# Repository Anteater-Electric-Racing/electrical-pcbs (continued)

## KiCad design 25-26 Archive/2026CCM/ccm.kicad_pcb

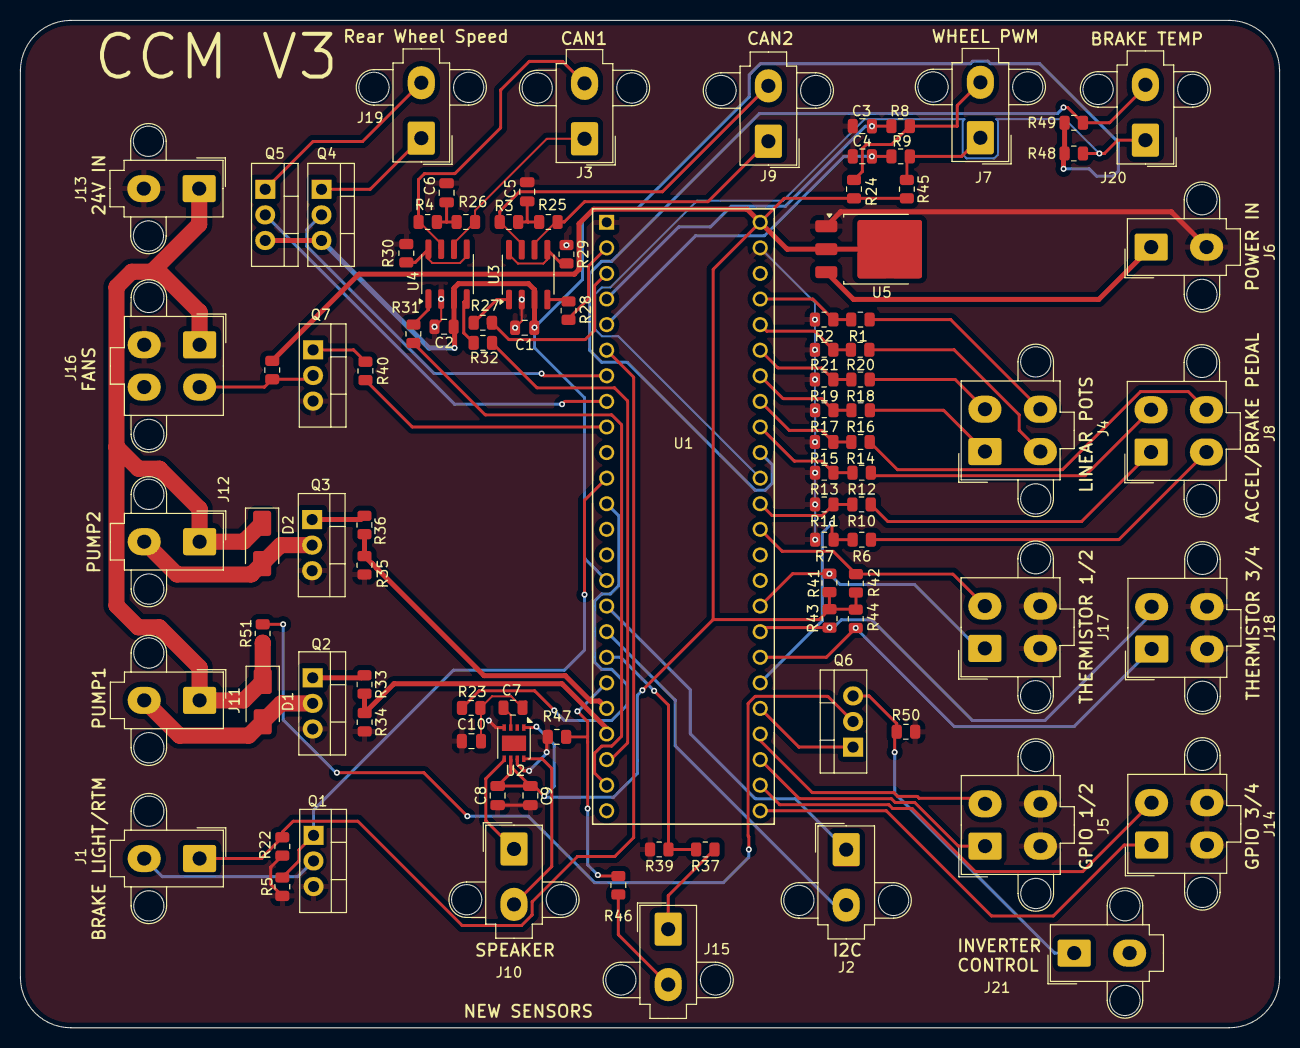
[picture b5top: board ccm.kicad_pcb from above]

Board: 2 copper layers, 125.0 x 100.0 mm, 96 parts (0 on the bottom side), 81 nets.

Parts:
C1, C2, C5, C6: 100 nF; C_0805_2012Metric
C3, C4: 0.01uF; C_0805_2012Metric
C7: 0.1uF; C_0805_2012Metric
C8: 1uF; C_0805_2012Metric
C9: 10uF; C_0805_2012Metric
C10: 10nF; C_0805_2012Metric
D1, D2: SS34; D_SMA
J1, J2, J3, J6, J7, J9, J10, J11, J12, J13, J15, J19, J20, J21: Conn_01x02_Socket; Molex_Mini-Fit_Jr_5566-02A2_2x01_P4.20mm_Vertical
J4, J5, J8, J14, J16, J17, J18: Conn_01x04_Socket; Molex_Mini-Fit_Jr_5566-04A2_2x02_P4.20mm_Vertical
Q1, Q2, Q3, Q4, Q5, Q6, Q7: IRLZ34N; TO-220-3_Vertical
R1, R6, R10, R12, R14, R16, R18, R20: 50k; R_0805_2012Metric
R2, R7, R11, R13, R15, R17, R19, R21: 97k; R_0805_2012Metric
R3, R4, R25, R26, R27, R28, R29, R30, R31, R32: 60; R_0805_2012Metric
R5, R22, R34, R35, R38, R41, R42, R43, R44, R47, R50, R51: 10k; R_0805_2012Metric
R8, R9: 10; R_0805_2012Metric
R23, R40: 1k; R_0805_2012Metric
R24, R45, R48, R49: 4.7k; R_0805_2012Metric
R33, R36: 220; R_0805_2012Metric
R37: 100k; R_0805_2012Metric
R39: 27k; R_0805_2012Metric
R46: 6.5k; R_0805_2012Metric
U1: Teensy4.1; CONN_4848-6000-CP_3MM
U2: PAM8302AAY; DFN-8-1EP_3x3mm_P0.65mm_EP1.55x2.4mm
U3, U4: SN65HVD230; SOIC-8_3.9x4.9mm_P1.27mm
U5: LM1117DT-5.0; TO-252-3_TabPin2

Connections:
+3.3V: C1.1, C2.1, Q4.3 (S), Q5.3 (S), R48.1, R49.1, U1.15 (3V3), U3.3 (VCC), U4.3 (VCC)
+5V: C8.1, C9.1, R24.2, R38.1, R41.2, R42.2, R43.2, R44.2, R45.2, U1.48 (VIN), U2.1 (~SD), U2.6 (VDD), U5.2 (VO)
CANH_1: J9.2, R3.1, U3.7 (CANH)
CANH_2: J3.2, R4.1, U4.7 (CANH)
CANL_1: J9.1, R25.2, U3.6 (CANL)
CANL_2: J3.1, R26.2, U4.6 (CANL)
CAN_RX_1: R28.1, U1.2 (0_RX1_CRX2_CS1)
CAN_RX_2: R32.1, U1.22 (30_CRX3)
CAN_TX_1: R27.1, U1.3 (1_TX1_CTX2_MISO1)
CAN_TX_2: R31.1, U1.23 (31_CTX3)
Fan+: D1.1 (K), D2.1 (K), J11.1, J12.1, J13.1, J16.1, R51.1
Fan_PWM: J16.2, Q7.2 (D), R38.2
GLV-: C1.2, C2.2, C3.2, C4.2, C5.2, C6.2, C8.2, C9.2, C10.1, J5.3, J5.4, J6.2, J13.2, J14.3, J14.4, J16.3, J17.3, J17.4, J18.3, J18.4, Q1.3 (S), Q2.3 (S), Q3.3 (S), Q7.3 (S), R2.2, R5.1, R7.2, R11.2, R13.2, R15.2, R17.2, R19.2, R21.2, R22.1, R29.1, R30.1, R34.2, R35.2, R39.2, R47.2, R50.2, U1.1 (GND), U1.47 (GND), U2.4 (IN-), U2.7 (GND), U3.2 (GND), U4.2 (GND), U5.1 (GND)
unnamed: C5.1, R3.2, R25.1
unnamed: C6.1, R4.2, R26.1
unnamed: C7.2, C10.2, R23.1
unnamed: Q1.1 (G), R5.2, U1.11 (9_OUT1C)
unnamed: Q2.1 (G), R33.1
unnamed: Q3.1 (G), R36.1
unnamed: Q4.2 (D), U1.7 (5_IN2)
unnamed: Q5.2 (D), U1.8 (6_OUT1D)
unnamed: Q6.2 (D), R51.2
unnamed: Q6.1 (G), U1.29 (37_CS)
unnamed: Q7.1 (G), R40.1
unnamed: C3.1, R8.2, U1.4 (2_OUT2)
unnamed: C4.1, R9.2, U1.5 (3_LRCLK2)
unnamed: R40.2, U1.9 (7_RX2_OUT1A)
unnamed: R10.2, R11.1, U1.37 (15_A1_RX3_SPDIF_IN)
unnamed: R12.2, R13.1, U1.40 (18_A4_SDA)
unnamed: R14.2, R15.1, U1.41 (19_A5_SCL)
unnamed: R16.2, R17.1, U1.42 (20_A6_TX5_LRCLK1)
unnamed: R18.2, R19.1, U1.43 (21_A7_RX5_BCLK1)
unnamed: R20.2, R21.1, U1.44 (22_A8_CTX1)
unnamed: R1.2, R2.1, U1.45 (23_A9_CRX1_MCLK1)
unnamed: R37.2, R39.1, U1.18 (26_A12_MOSI1)
unnamed: R46.2, R47.1, U1.19 (27_A13_SCK1)
unnamed: R35.1, R36.2, U1.20 (28_RX7)
unnamed: R33.2, R34.1, U1.21 (29_TX7)
unnamed: R6.2, R7.1, U1.30 (38_CS1_IN1)
unnamed: C7.1, U2.3 (IN+)
unnamed: R27.2, U3.1 (D)
unnamed: R28.2, U3.4 (R)
unnamed: R29.2, U3.5 (Vref), U3.8 (Rs)
unnamed: R31.2, U4.1 (D)
unnamed: R32.2, U4.4 (R)
unnamed: R30.2, U4.5 (Vref), U4.8 (Rs)
PWM_in_1: J7.1, R9.1, R45.1
PWM_in_2: J7.2, R8.1, R24.1
Pump1-: D1.2 (A), J11.2, Q2.2 (D)
Pump2-: D2.2 (A), J12.2, Q3.2 (D)
Vin: J6.1, U5.3 (VI)
acc_ped_1: J8.4, R14.1
acc_ped_2: J8.2, R12.1
brake_1: J8.1, R10.1
brake_2: J8.3, R6.1
brake_light: J1.2, Q1.2 (D)
brake_temp_scl: J20.1, R48.2, U1.38 (16_A2_RX4_SCL1)
brake_temp_sda: J20.2, R49.2, U1.39 (17_A3_TX4_SDA1)
gpio1: J5.2, U1.28 (36_CS)
gpio2: J5.1, U1.27 (35_TX8)
gpio3: J14.2, U1.26 (34_RX8)
gpio4: J14.1, U1.25 (33_MCLK2)
i2c_SCL: J2.1, U1.16 (24_A10_TX6_SCL2)
i2c_SDA: J2.2, U1.17 (25_A11_RX6_SDA2)
kl15: J21.1, Q6.3 (S), R50.1
lin_pot_1: J4.4, R1.1
lin_pot_2: J4.3, R20.1
lin_pot_3: J4.2, R18.1
lin_pot_4: J4.1, R16.1
ready_to_drive_button: J1.1, R22.2, U1.6 (4_BCLK2)
shock_travel: J15.2, R46.1
speaker+: J10.1, U2.5 (OUT+)
speaker-: J10.2, U2.8 (OUT-)
speaker_pwm: R23.2, U1.12 (10_CS_MQSR)
steering_angle: J15.1, R37.1
thermistor1+: J17.2, R41.1, U1.36 (14_A0_TX3_SPDIF_OUT)
thermistor2+: J17.1, R42.1, U1.33 (41_A17)
thermistor3+: J18.2, R43.1, U1.32 (40_A16)
thermistor4+: J18.1, R44.1, U1.31 (39_MISO1_OUT1A)
wheelspeed1: J19.1, Q4.1 (G)
wheelspeed2: J19.2, Q5.1 (G)

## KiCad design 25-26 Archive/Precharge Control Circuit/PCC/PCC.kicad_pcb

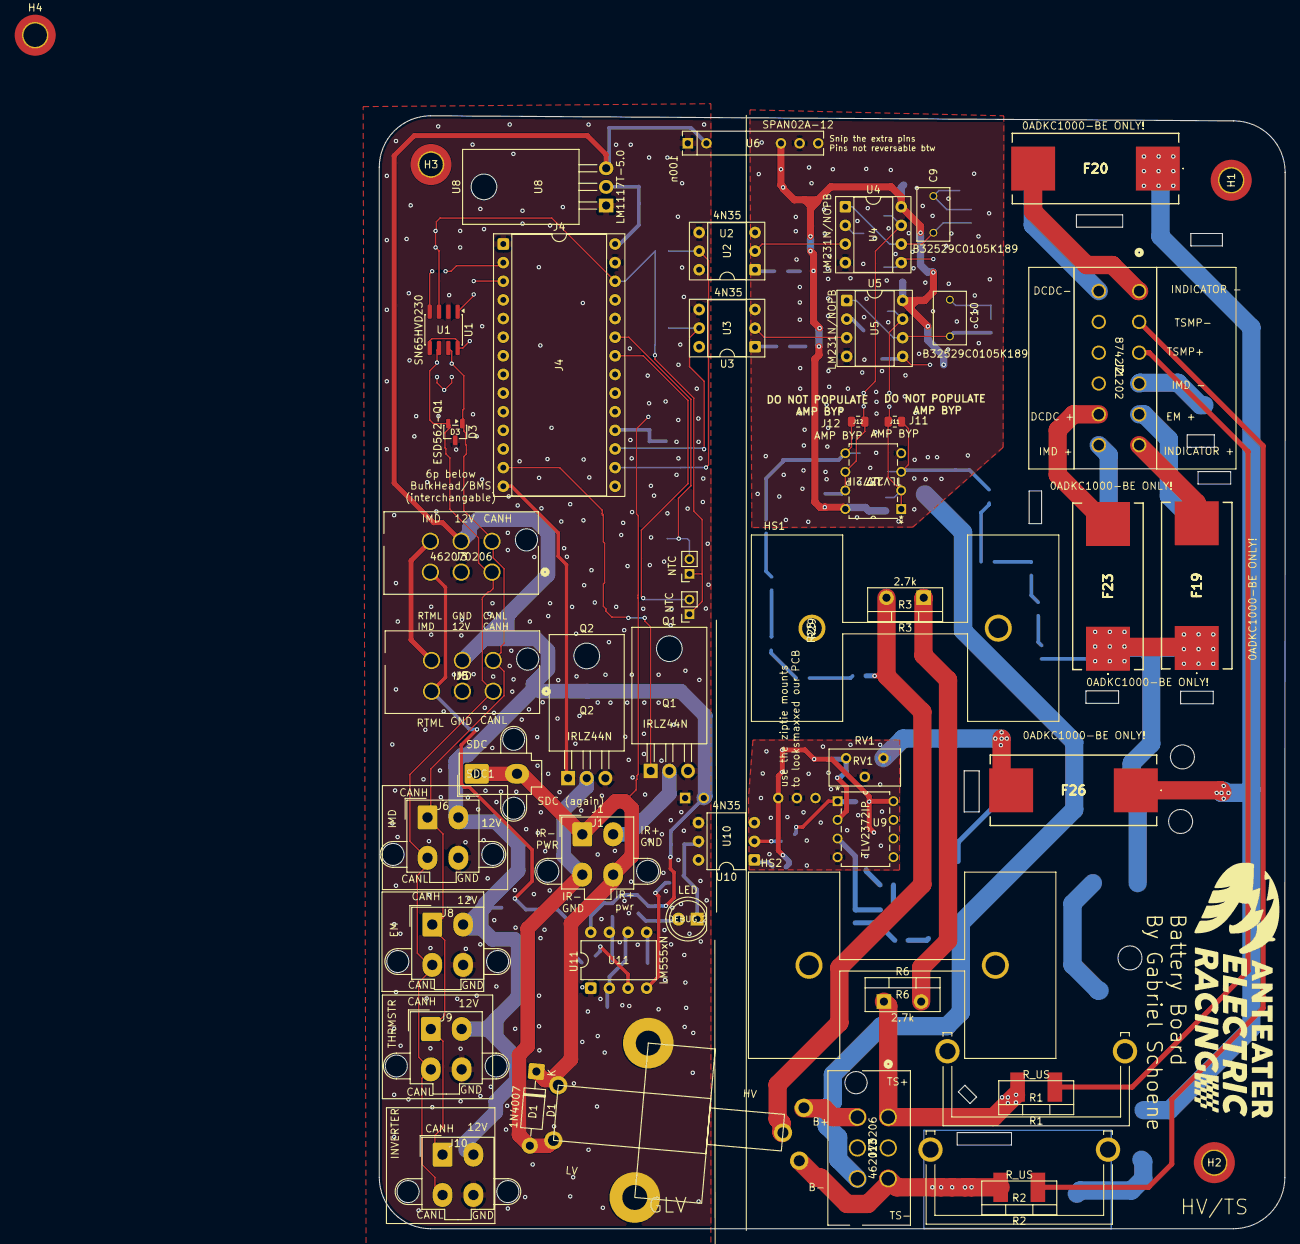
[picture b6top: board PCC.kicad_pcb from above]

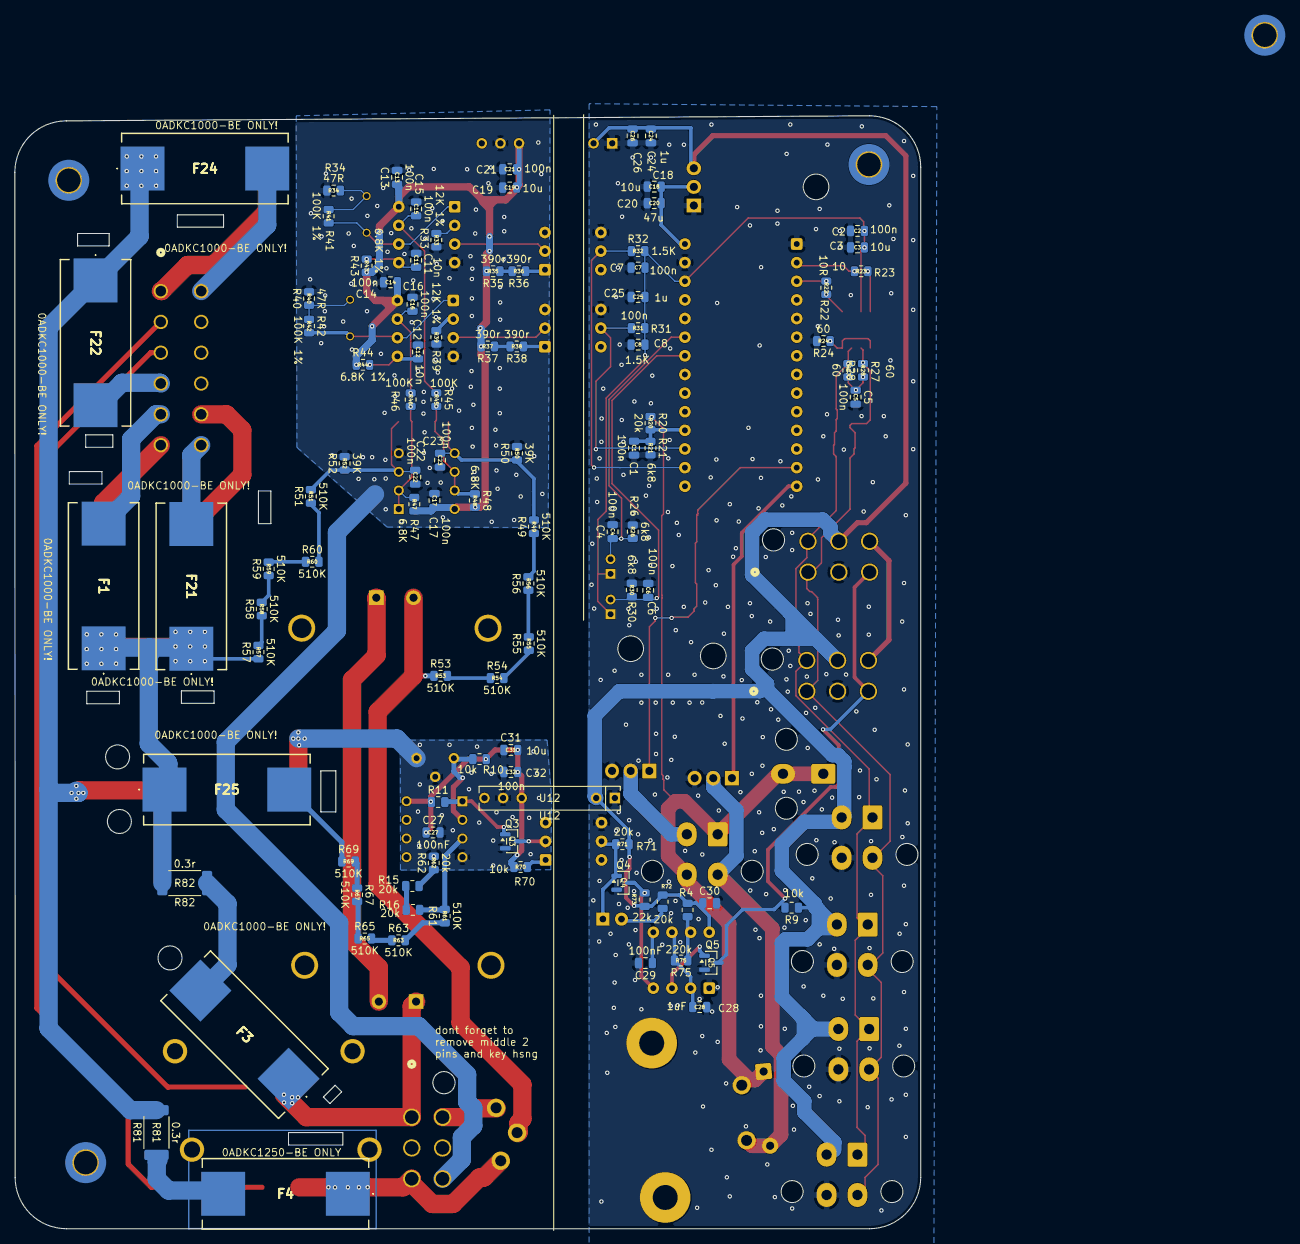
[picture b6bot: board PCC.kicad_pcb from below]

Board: 2 copper layers, 123.5 x 151.7 mm, 150 parts (99 on the bottom side), 93 nets.

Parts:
C1, C2, C4, C5, C6, C7, C8, C13, C14, C15, C16, C17, C21, C22, C23, C26, C32: 100n; C_0805_2012Metric
C3, C18, C19, C31: 10u; C_0805_2012Metric
C9, C10: B32529C0105K189; CAPRR500W50L730T450H950
C11, C12: 10n; C_0805_2012Metric
C20: 47u; C_0805_2012Metric
C24, C25: 1u; C_0805_2012Metric
C27, C29, C30: 100nF; C_0805_2012Metric
C28: 1uF; C_0805_2012Metric
D1: 1N4007; D_DO-41_SOD81_P10.16mm_Horizontal
D3: ESD562-Q1; SOT-23-3
DEBUG_2: LED; LED_D5.0mm
F1, F19, F20, F21, F22, F23, F24, F25, F26: 1A; 5x20fuseblock
F3, F4: 1.25; 5x20fuseblock
H1, H2, H3, H4: MountingHole_Pad; MountingHole_3.2mm_M3_DIN965_Pad_TopBottom
HS1, HS2: Heatsink_Pad; heatsink
HS3, HS4: Heatsink_Pad; smolsink
J1: Conn_01x04_Socket; Molex_Mini-Fit_Jr_5566-04A2_2x02_P4.20mm_Vertical
J2: 874271202; 12pSTminifit
J3, J13: 462070206; 6pMinifitJR
J4: Conn_02x14_Counter_Clockwise; DIP-28_W15.24mm_Socket
J5: IMD; 6pMinifitJR
J6: Thermistor Expansion; Molex_Mini-Fit_Jr_5566-04A2_2x02_P4.20mm_Vertical
J8: BMS; Molex_Mini-Fit_Jr_5566-04A2_2x02_P4.20mm_Vertical
J9: EnergyMeter; Molex_Mini-Fit_Jr_5566-04A2_2x02_P4.20mm_Vertical
J10: INVTR; Molex_Mini-Fit_Jr_5566-04A2_2x02_P4.20mm_Vertical
J11, J12: AMP BYP; R_0805_2012Metric
K1: Relay_SPDT; RH3_Mount
Q1, Q2: IRLZ44N; TO-220-3_Horizontal_TabDown
Q3, Q4, Q5: Q_NMOS_GSD; SOT-23
R1, R2: R_US; TO-220-2_Vertical-SMD
R3, R6: 2.7k; TO-220-2_Vertical
R4, R73: 22k; R_0805_2012Metric
R9, R10, R11, R70: 10k; R_0805_2012Metric
R15, R16, R20, R62, R71, R72: 20k; R_0805_2012Metric
R21, R26, R30: 6k8; R_0805_2012Metric
R22: 10R; R_0805_2012Metric
R23: 10; R_0805_2012Metric
R24, R27, R28: 60; R_0805_2012Metric
R25, R29: NTC; PinSocket_1x02_P2.00mm_Vertical
R31, R32: 1.5K; R_0805_2012Metric
R33, R39: 12K 1%; R_0805_2012Metric
R34, R40: 47R; R_0805_2012Metric
R35, R36, R37, R38: 390r; R_0805_2012Metric
R41, R42: 100K 1%; R_0805_2012Metric
R43, R44: 6.8K 1%; R_0805_2012Metric
R45, R46: 100K; R_0805_2012Metric
R47, R48: 6.8K; R_0805_2012Metric
R49, R51, R53, R54, R55, R56, R57, R58, R59, R60, R61, R63, R65, R67, R69: 510K; R_0805_2012Metric
R50, R52: 39K; R_0805_2012Metric
R75: 220k; R_0805_2012Metric
R81, R82: 0.3r; R_2512_6332Metric_Pad1.40x3.35mm_HandSolder
RV1: 1k default (1-5k); Potentiometer_Bourns_3296Y_Vertical
SDC1: Conn_01x02_Socket; Molex_Mini-Fit_Jr_5566-02A2_2x01_P4.20mm_Vertical
U1: SN65HVD230; SOIC-8_3.9x4.9mm_P1.27mm
U2, U3: 4N35; DIP-6_W7.62mm_Socket
U4, U5: DIP-8_W7.62mm_Socket
U6, U12: isoDCDC(removedPins)
U7, U9: TLV2372IP; P8
U8: LM1117T-5.0; TO-220-3_Horizontal_TabDown
U10: 4N35; DIP-6_W7.62mm
U11: LM555xN; DIP-8_W7.62mm

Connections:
12V_UNISO: C27.1, C31.2, C32.2, R10.1, R11.1, R70.1, U9.8 (VDD), U12.6 (+Vout)
+3.3V: C2.1, C3.1, C7.1, C8.1, C25.1, J4.26, R25.1, R29.1, R31.2, R32.2, U1.3 (VCC)
+5V: C18.1, C20.1, J4.28, U8.2 (VO)
+12 ISO: C13.1, C14.1, C17.1, C19.2, C21.2, R35.2, R37.2, R43.1, R44.1, R47.2, R48.2, U4.8 (VS), U5.8 (VS), U6.6 (+Vout), U7.8 (VDD)
/FusedTS + (IMD): F21.2, J2.12
/FusedTS + (expansion): F23.2, J2.11
/FusedTS + (indicator): F19.2, J2.6
/FusedTS - (IMD): F22.2, J2.4
/FusedTS - (expansion): F24.2, J2.7
/FusedTS - (indicator): F20.2, J2.1
/FusedTS+ (EM): F1.2, J2.5
/NTC 1: C4.1, J4.23, R25.2, R26.1
/NTC 2: C6.1, J4.22, R29.2, R30.1
/SDN signal: C1.1, J4.18, R20.2, R21.1
/TSMP+: J2.3, R1.1
/TSMP-: J2.2, R2.1
B+_in: J13.4, K1.14
CANH: D3.1 (K), J3.4, J5.4, J6.1, J8.1, J9.1, J10.1, R27.1, U1.7 (CANH)
CANL: D3.2 (K), J3.1, J5.1, J6.3, J8.3, J9.3, J10.3, R28.2, U1.6 (CANL)
CANRX: J4.2, R23.1
CANTX: J4.3, R22.2
Freq_Accumulator: J4.16, R32.1, U2.5
Freq_TS: J4.17, R31.1, U3.5
GLV+: C24.1, C26.1, C30.1, J3.5, J5.5, J6.2, J8.2, J9.2, J10.2, R4.1, R9.1, R71.1, R72.1, R73.1, U6.2 (+Vin), U8.3 (VI), U11.8 (VCC), U12.2 (+Vin)
GLV-: C1.2, C2.2, C3.2, C4.2, C5.2, C6.2, C7.2, C8.2, C18.2, C20.2, C24.2, C25.2, C26.2, C28.2, C29.2, C30.2, D3.3 (A), J3.2, J4.1, J4.27, J5.2, J6.4, J8.4, J9.4, J10.4, Q1.3 (S), Q2.3 (S), Q4.2 (S), Q5.2 (S), R21.2, R24.2, R26.2, R30.2, U1.2 (GND), U2.4, U3.4, U6.1 (-Vin), U8.1 (GND), U10.4, U11.1 (GND), U12.1 (-Vin)
GND ISO: C11.2, C12.2, C13.2, C14.2, C15.2, C16.2, C17.2, C19.1, C21.1, C22.2, C23.2, J13.6, R33.1, R34.2, R39.1, R40.2, R50.2, R52.2, U4.4 (GND), U5.4 (GND), U6.7 (-Vout), U7.4 (GND)
HighVoltage+: F25.2, R69.1
HighVoltage-: C27.2, C31.1, C32.1, F26.2, Q3.2 (S), R62.2, RV1.1, RV1.2, U9.4 (GND), U12.7 (-Vout)
IMD_Fault: J3.6, J5.6
IR+ CTRL: J4.13, Q1.1 (G)
IR+_GND: J1.2, Q1.2 (D)
IR-_GND: D1.2 (A), J1.3, K1.A2, Q2.2 (D)
unnamed: C5.1, R27.2, R28.1
unnamed: C9.1, R34.1, R41.1
unnamed: C10.1, R40.1, R42.1
unnamed: DEBUG_2.2 (A), R72.2
unnamed: DEBUG_2.1 (K), Q4.1 (G), R71.2, U10.5
unnamed: F3.2, R82.1
unnamed: F4.2, R81.1
unnamed: Q3.3 (D), U10.2
unnamed: Q3.1 (G), R11.2, U9.1 (1OUT)
unnamed: Q4.3 (D), R73.2, U11.4 (R)
unnamed: Q5.1 (G), U11.3 (Q)
unnamed: R3.1, R6.2
unnamed: R15.1, R16.2
unnamed: R15.2, R62.1
unnamed: R35.1, R36.2
unnamed: R36.1, U2.1
unnamed: R37.1, R38.2
unnamed: R38.1, U3.1
unnamed: R49.1, R56.2
unnamed: R51.1, R60.2
unnamed: R53.2, R54.1
unnamed: R54.2, R55.1
unnamed: R55.2, R56.1
unnamed: R57.2, R58.1
unnamed: R58.2, R59.1
unnamed: R59.2, R60.1
unnamed: R61.1, R63.2
unnamed: R63.1, R65.2
unnamed: R65.1, R67.2
unnamed: R67.1, R69.2
unnamed: R70.2, U10.1
unnamed: R22.1, U1.1 (D)
unnamed: R23.2, U1.4 (R)
unnamed: R24.1, U1.5 (Vref), U1.8 (Rs)
unnamed: C15.1, R45.1, U4.7 (COMPIN)
unnamed: U2.2, U4.3 (FOUT)
unnamed: C9.2, R41.2, U4.1 (IOUT), U4.6 (THRESH)
unnamed: R33.2, U4.2 (IREF)
unnamed: C11.1, R43.2, U4.5 (RC)
unnamed: C16.1, R46.1, U5.7 (COMPIN)
unnamed: U3.2, U5.3 (FOUT)
unnamed: C10.2, R42.2, U5.1 (IOUT), U5.6 (THRESH)
unnamed: R39.2, U5.2 (IREF)
unnamed: C12.1, R44.2, U5.5 (RC)
unnamed: C22.1, J11.2, R51.2, R52.1, U7.3 (1IN+)
unnamed: J11.1, R46.2, R47.1, U7.1 (1OUT), U7.2 (1IN-)
unnamed: C23.1, J12.2, R49.2, R50.1, U7.5 (2IN+)
unnamed: J12.1, R45.2, R48.1, U7.6 (2IN-), U7.7 (2OUT)
unnamed: C29.1, U11.5 (CV)
unnamed: R4.2, R75.1, U11.7 (DIS)
unnamed: C28.1, R75.2, U11.2 (TR), U11.6 (THR)
PreDis_IR-: J4.14, Q2.1 (G)
RTM_SIG: J3.3, J5.3, Q5.3 (D), R9.2
Shutdown_in: D1.1 (K), J1.1, J1.4, K1.A1, R20.1, SDC1.1, SDC1.2
TS+: F1.1, F19.1, F21.1, F23.1, F25.1, R57.1, R82.2
TS+ unfused: F3.1, J13.1, R1.2, R6.1
TS-: F20.1, F22.1, F24.1, F26.1, R81.2
TS- unfused: F4.1, J13.3, K1.12, R2.2
V_BIAS: R10.2, RV1.3, U9.2 (1IN-)
V_SNS: R16.1, R61.2, U9.3 (1IN+)
Vin_Accu: K1.11, R3.2, R53.1

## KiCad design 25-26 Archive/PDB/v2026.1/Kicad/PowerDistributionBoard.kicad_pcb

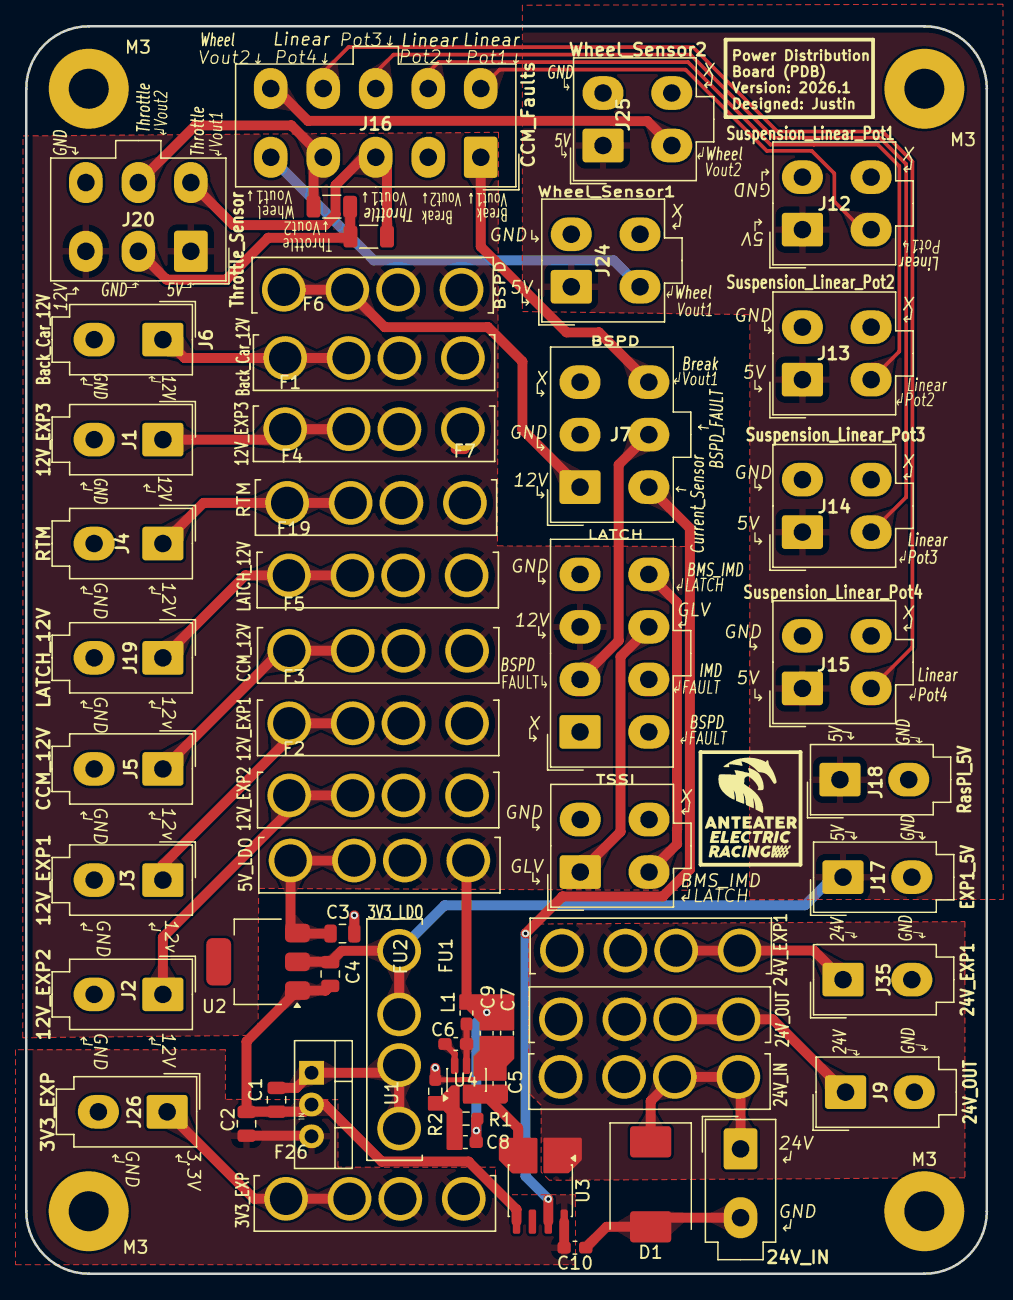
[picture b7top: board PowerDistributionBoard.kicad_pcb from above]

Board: 2 copper layers, 76.8 x 99.8 mm, 62 parts (0 on the bottom side), 36 nets.

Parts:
C1: 0.47uF; C_0805_2012Metric
C2: 33uF; C_0805_2012Metric
C3: 1uF; C_0805_2012Metric
C4: 2.2uF; C_0805_2012Metric
C5: 10uF; C_0603_1608Metric_Pad1.08x0.95mm_HandSolder
C6, C10: 100nF; C_0603_1608Metric_Pad1.08x0.95mm_HandSolder
C7, C9: 22uF; C_0603_1608Metric_Pad1.08x0.95mm_HandSolder
C8: 56pF; C_0603_1608Metric_Pad1.08x0.95mm_HandSolder
D1: 1.5SMCxxA; D_SMC
F1: 12V_EXP3; FUSE_3522-2
F2: 12V_EXP2; FUSE_3522-2
F3: 12V_EXP1; FUSE_3522-2
F4: RTM; FUSE_3522-2
F5: CCM_12V; FUSE_3522-2
F6: Back_Car_12V; FUSE_3522-2
F7: BSPD; FUSE_3522-2
F8: 24V_OUT; FUSE_3522-2
F9: 24V_IN; FUSE_3522-2
F19: LATCH_12V; FUSE_3522-2
F26: 3V3_EXP; FUSE_3522-2
F35: 24V_EXP1; FUSE_3522-2
FU1: 3V3_LDO; FUSE_3522-2
FU2: 5V_LDO; FUSE_3522-2
J1: 12V_EXP3; Molex_Mini-Fit_Jr_5566-02A_2x01_P4.20mm_Vertical
J2: 12V_EXP2; Molex_Mini-Fit_Jr_5566-02A_2x01_P4.20mm_Vertical
J3: 12V_EXP1; Molex_Mini-Fit_Jr_5566-02A_2x01_P4.20mm_Vertical
J4: RTM; Molex_Mini-Fit_Jr_5566-02A_2x01_P4.20mm_Vertical
J5: CCM_12V; Molex_Mini-Fit_Jr_5566-02A_2x01_P4.20mm_Vertical
J6: Back_Car_12V; Molex_Mini-Fit_Jr_5566-02A_2x01_P4.20mm_Vertical
J7: BSPD; Molex_Mini-Fit_Jr_5566-06A_2x03_P4.20mm_Vertical
J8: TSSI; Molex_Mini-Fit_Jr_5566-04A_2x02_P4.20mm_Vertical
J9: 24V_OUT; Molex_Mini-Fit_Jr_5566-02A_2x01_P4.20mm_Vertical
J10: 24V_IN; Molex_Mini-Fit_Jr_5566-02A_2x01_P4.20mm_Vertical
J11: LATCH; Molex_Mini-Fit_Jr_5566-08A_2x04_P4.20mm_Vertical
J12: Suspension_Linear_Pot1; Molex_Mini-Fit_Jr_5566-04A_2x02_P4.20mm_Vertical
J13: Suspension_Linear_Pot2; Molex_Mini-Fit_Jr_5566-04A_2x02_P4.20mm_Vertical
J14: Suspension_Linear_Pot3; Molex_Mini-Fit_Jr_5566-04A_2x02_P4.20mm_Vertical
J15: Suspension_Linear_Pot4; Molex_Mini-Fit_Jr_5566-04A_2x02_P4.20mm_Vertical
J16: CCM_Faults; Molex_Mini-Fit_Jr_5566-10A_2x05_P4.20mm_Vertical
J17: EXP1_5V; Molex_Mini-Fit_Jr_5566-02A_2x01_P4.20mm_Vertical
J18: RasPI_5V; Molex_Mini-Fit_Jr_5566-02A_2x01_P4.20mm_Vertical
J19: LATCH_12V; Molex_Mini-Fit_Jr_5566-02A_2x01_P4.20mm_Vertical
J20: Throttle_Sensor; Molex_Mini-Fit_Jr_5566-06A_2x03_P4.20mm_Vertical
J24: Wheel_Sensor1; Molex_Mini-Fit_Jr_5566-04A_2x02_P4.20mm_Vertical
J25: Wheel_Sensor2; Molex_Mini-Fit_Jr_5566-04A_2x02_P4.20mm_Vertical
J26: 3V3_EXP; Molex_Mini-Fit_Jr_5566-02A_2x01_P4.20mm_Vertical
J35: 24V_EXP1; Molex_Mini-Fit_Jr_5566-02A_2x01_P4.20mm_Vertical
L1: 10uH; L_0603_1608Metric_Pad1.05x0.95mm_HandSolder
M3, M3#2, M3#3, M3#4: MountingHole M3; MountingHole_3.2mm_M3_Pad
R1: 249k; R_0603_1608Metric_Pad0.98x0.95mm_HandSolder
R2: 18k; R_0603_1608Metric_Pad0.98x0.95mm_HandSolder
R3, R4: 10K; R_1206_3216Metric
U1: 5to3.3_Linear_Regulator; TO-220-3_Vertical
U2: TLV76150DCYR; SOT-223
U3: ACS711xLCTR-12AB; SOIC-8_3.9x4.9mm_P1.27mm
U4: AP63200WU; TSOT-23-6

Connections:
3.3V: C2.1, C10.2, F26.2, U1.3 (VO), U3.8 (VCC)
5V: C4.1, FU1.1, J12.1, J13.1, J14.1, J15.1, J17.1, J18.1, J24.1, J25.1, U2.2 (OUT)
12V: C7.1, C8.1, C9.1, F1.2, F2.2, F3.2, F4.2, F5.2, F6.2, F7.1, F19.2, FU2.2, J11.3, J20.1, J20.3, L1.2, R1.1
24V: F8.2, F9.1, F35.2, U3.1 (IP+), U3.2 (IP+)
/BST: C6.2, U4.6 (BST)
/BUCK_IN: C5.1, U3.3 (IP-), U3.4 (IP-), U4.2 (EN), U4.3 (IN)
/Back_Car_12V: F6.1, J6.1
/FB: C8.2, R1.2, R2.1, U4.1 (FB)
/Fuse_5to3.3: C1.1, FU1.2, U1.1 (VI)
/Fuse_12to5: C3.1, FU2.1, U2.3 (IN)
/Fuse_24V_OUT: F8.1, J9.1
/Fuse_BSPD: F7.2, J7.1
/Fuse_CCM_12V: F5.1, J5.1
/Fuse_EXP1_12V: F3.1, J3.1
/Fuse_EXP1_24V: F35.1, J35.1
/Fuse_EXP2_12V: F2.1, J2.1
/Fuse_EXP3_12V: F1.1, J1.1
/Fuse_EXP_3V3: F26.1, J26.1
/Fuse_LATCH_12V: F19.1, J19.1
/Fuse_RTM: F4.1, J4.1
/SW: C6.1, L1.1, U4.5 (SW)
BSPD_FAULT: J7.5, J11.2
Brake_Sensor_Vout1: J7.6, J16.1
Current_Sensor: J7.4, U3.7 (VIOUT)
GLV: J8.1, J11.7
GND: C1.2, C2.2, C3.2, C4.2, C5.2, C7.2, C9.2, C10.1, D1.2 (A2), J1.2, J2.2, J3.2, J4.2, J5.2, J6.2, J7.2, J8.2, J9.2, J10.2, J11.4, J12.2, J13.2, J14.2, J15.2, J17.2, J18.2, J19.2, J20.2, J20.6, J24.2, J25.2, J26.2, J35.2, R2.2, R3.2, R4.2, U1.2 (GND), U2.1 (GND), U3.5 (GND), U4.4 (GND)
Linear_Pot1: J12.3, J16.6
Linear_Pot2: J13.3, J16.7
Linear_Pot3: J14.3, J16.8
Linear_Pot4: J15.3, J16.9
unnamed: D1.1 (A1), F9.2, J10.1
Throttle_Sensor_Vout1: J16.3, J20.4, R3.1
Throttle_Sensor_Vout2: J16.4, J20.5, R4.1
Wheel_Sensor_Vout1: J16.5, J24.3
Wheel_Sensor_Vout2: J16.10, J25.3
bms_imd_latch_only: J8.3, J11.8
